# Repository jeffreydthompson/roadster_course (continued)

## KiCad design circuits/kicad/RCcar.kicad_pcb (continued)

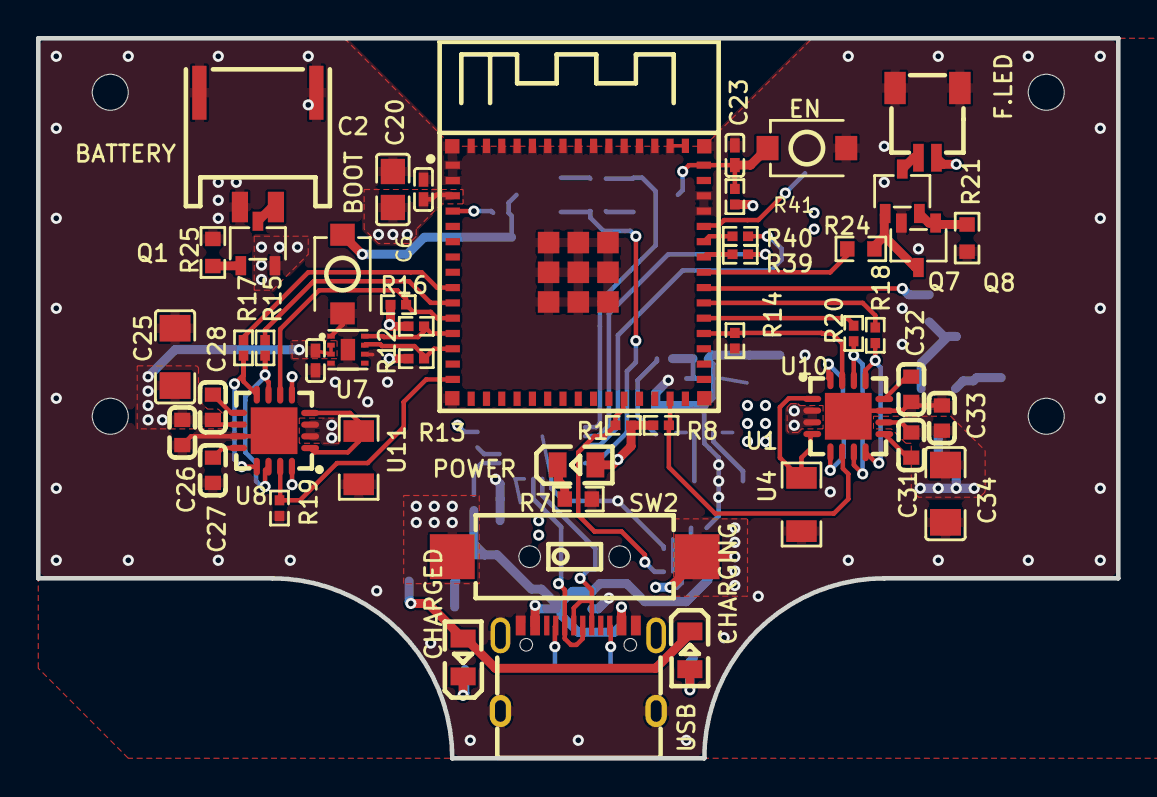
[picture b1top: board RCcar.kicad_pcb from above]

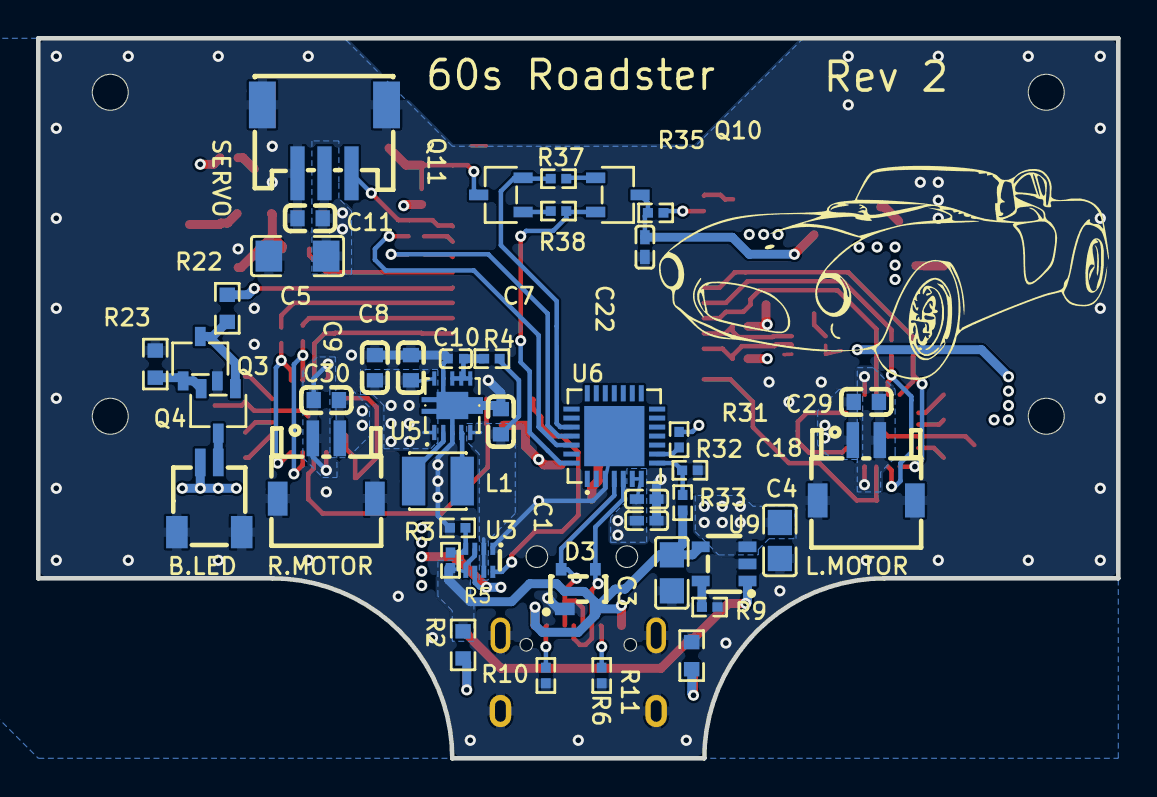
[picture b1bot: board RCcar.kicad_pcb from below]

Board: 4 copper layers, 60.0 x 40.0 mm, 95 parts (43 on the bottom side), 68 nets.

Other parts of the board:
Hole_gge8842846562267455: Hole_gge8842846562267455
Hole_gge8842846562267458: Hole_gge8842846562267458
Hole_gge8842846562267461: Hole_gge8842846562267461
Hole_gge8842846562267464: Hole_gge8842846562267464

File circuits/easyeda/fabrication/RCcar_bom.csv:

ID,Name,Designator,Footprint,Quantity,Manufacturer Part,Manufacturer,Supplier,Supplier Part,Price
"1","SM02B-SRSS-TB (LF)(SN)","B.LED,F.LED","CONN-SMD_2P-P1.00_SM02B-SRSS-TB-LF-SN","2","SM02B-SRSS-TB(LF)(SN)","JST","LCSC","C160402","0.133"
"2","PH2.0-2PWB","BATTERY","CONN-SMD_2P-P2.00_PH2.0-SPWB","1","PH-2P卧贴","BOOMELE(博穆精密)","LCSC","C47647","0.062"
"3","TS-1088-AR02016","BOOT,EN","SW-SMD_L3.9-W3.0-P4.45","2","TS-1088-AR02016","XUNPU(讯普)","LCSC","C720477","0.053"
"4","4.7uF","C1","C0402","1","CL05A475MP5NRNC","SAMSUNG(三星)","LCSC","C23733","0.017"
"5","22uF","C2","C0805","1","CL21A226MAQNNNE","SAMSUNG(三星)","LCSC","C45783","0.222"
"6","4.7uF","C3,C4","C0805","2","CL21A475KAQNNNE","SAMSUNG(三星)","LCSC","C1779","0.035"
"7","22uF","C5,C25,C34","C1206","3","HGC1206R7226K160NSPJ","Chinocera(华瓷)","LCSC","C7472972","0.156"
"8","100nF","C6,C18,C20,C22,C23","C0402_NEW","5","CL05B104KO5NNNC","SAMSUNG","LCSC","C1525","0.005"
"9","10uF","C7,C8,C9","C0603","3","CL10B106MQ8NRNC","SAMSUNG(三星)","LCSC","C3039698","0.091"
"10","100nF","C10","C0402","1","CL05B104KO5NNNC","SAMSUNG(三星)","LCSC","C1525","0.005"
"11","100nF","C11,C27,C32","C0603","3","CL10B104KO8NNNC","SAMSUNG(三星)","LCSC","C66501","0.009"
"12","2.2uF","C26,C33","C0603","2","CL10B225KP8NNNC","SAMSUNG(三星)","LCSC","C100082","0.028"
"13","10nF","C28,C31","C0603","2","CC0603KRX7R7BB103","YAGEO(国巨)","LCSC","C519406","0.006"
"14","100nF","C29,C30","C0603","2","CC0603KRX7R9BB104","YAGEO(国巨)","LCSC","C14663","0.014"
"15","0805G (Green)","CHARGED","LED0805-R-RD","1","KT-0805G","KENTO","LCSC","C2297","0.017"
"16","17-21SUYC/TR8","CHARGING","LED0805-R-RD","1","KT-0805黄灯","KENTO","LCSC","C2296","0.012"
"17","SP0503BAHTG","D3","SOT-143_L2.9-W1.3-P1.92-LS2.3-BR","1","SP0503BAHTG","Littelfuse","LCSC","C7074","0.264"
"18","2.2uH","L1","IND-SMD_L3.0-W3.0_FNR30XXS","1","SPH3015H2R2MT","Sunlord(顺络)","LCSC","C370424",""
"19","S2B-ZR-SM4A-TF(LF)(SN)","L.MOTOR,R.MOTOR","CONN-SMD_S2B-ZR-SM4A","2","S2B-ZR-SM4A-TF(LF)(SN)","JST","LCSC","C265329","0.222"
"20","FC-2012HRK-620D","POWER","LED0805-R-RD","1","NCD0805R1","国星光电","LCSC","C84256","0.014"
"21","SI2305CDS","Q1","SOT-23-3_L2.9-W1.6-P1.90-LS2.8-BR","1","SI2305CDS","TECH PUBLIC(台舟)","LCSC","C5182095","0.102"
"22","2SC2712-GR,LF(T","Q3,Q4,Q7,Q8","SOT-23-3_L2.9-W1.6-P1.90-LS2.8-BR","4","2SC2712-GR,LF(T","TOSHIBA","LCSC","C83447","0.031"
"23","SS8050-G","Q10,Q11","SOT-23-3_L2.9-W1.6-P1.90-LS2.8-BR","2","SS8050-G","CJ(江苏长电/长晶)","LCSC","C164886","0.017"
"24","5.1kΩ","R1,R5,R6,R9","R0402","4","0402WGF5101TCE","UNI-ROYAL(厚声)","LCSC","C25905","0.002"
"25","10kΩ","R2,R3,R8,R14,R16,R19,R37,R38,R41","R0402","9","0402WGF1002TCE","UniOhm","LCSC","C25744","0.003"
"26","100Ω","R4","R0402","1","0402WGF1000TCE","UNI-ROYAL(厚声)","LCSC","C25076","0.001"
"27","470Ω","R7,R10,R11","R0603","3","0603WAF4700T5E","UNI-ROYAL(厚声)","LCSC","C23179","0.002"
"28","4.7kΩ","R12,R13","R0402","2","0402WGF4701TCE","UNI-ROYAL(厚声)","LCSC","C25900","0.003"
"29","100Ω","R15,R17,R18,R20","R0402","4","RC0402FR-07100RL","YAGEO(国巨)","LCSC","C106232","0.002"
"30","22Ω","R21,R23","R0603","2","0603WAF220JT5E","UNI-ROYAL(厚声)","LCSC","C23345","0.002"
"31","1kΩ","R22,R24","R0603","2","MCT06030C1001FP500","Vishay Intertech","LCSC","C161809","0.042"
"32","100kΩ","R25","R0603","1","0603WAF1003T5E","UNI-ROYAL(厚声)","LCSC","C25803","0.003"
"33","1kΩ","R31","R0402","1","0402WGF1001TCE","UniOhm","LCSC","C11702","0.003"
"34","47.5kΩ","R32","R0402","1","0402WGF4752TCE","UniOhm","LCSC","C25896","0.002"
"35","22.1kΩ","R33","R0402","1","0402WGF2212TCE","UniOhm","LCSC","C43473","0.002"
"36","22Ω","R35","R0402","1","0402WGF220JTCE","UniOhm","LCSC","C25092","0.003"
"37","0Ω","R39,R40","R0402","2","0402WGF0000TCE","UniOhm","LCSC","C17168","0.003"
"38","HCZZ0323-3","SERVO","CONN-SMD_3P-P1.50_HCZZ0323-3","1","HCZZ0323-3","HC(虹成电子)","LCSC","C7433559","0.02"
"39","MS-12D08G3.5","SW2","SW-TH_MS-12D08G3.5","1","MS-12D08G3.5","HOOYA(皓宇电子)","LCSC","C2939255","0.154"
"40","ESP32-S3-MINI-1-N8","U1","BULETM-SMD_ESP32-S3-MINI-1-N8","1","ESP32-S3-MINI-1-N8","ESPRESSIF(乐鑫)","LCSC","C2913206","4.756"
"41","TPS2116DRLR","U3","SOT-583-8_L2.1-W1.6-P0.50-LS1.6-BL","1","TPS2116DRLR","TI(德州仪器)","LCSC","C3235557","0.403"
"42","50mΩ","U4,U11","R1206","2","FRM121WFR050TM","FOJAN(富捷)","LCSC","C7467249","0.035"
"43","TPS63001DRCR","U5","VSON-10_L3.0-W3.0-P0.50-TL-EP_TPS62410DRCR","1","TPS63001DRCR","TI(德州仪器)","LCSC","C28060","1.618"
"44","CP2102N-A02-GQFN28R","U6","QFN-28_L5.0-W5.0-P0.50-TL-EP3.3","1","CP2102N-A02-GQFN28R","SILICON LABS(芯科)","LCSC","C964632","1.837"
"45","MAX17048G+T10","U7","TDFN-8_L2.0-W2.0-P0.50-BL-EP1.2","1","MAX17048G+T10","ADI(亚德诺)/MAXIM(美信)","LCSC","C2682616","2.165"
"46","DRV8833RTYR","U8,U10","QFN-16_L4.0-W4.0-P0.65-TL-EP2.6","2","DRV8833RTYR","TI(德州仪器)","LCSC","C154936","2.411"
"47","MCP73831T-2ACI/OT","U9","SOT-23-5_L3.0-W1.7-P0.95-LS2.8-BR","1","MCP73831T-2ACI/OT","Microchip Tech","LCSC","C424093","0.791"
"48","TYPE-C 16PIN 2MD(073)","USB","USB-C-SMD_TYPE-C-6PIN-2MD-073","1","TYPE-C 16PIN 2MD(073)","SHOU HAN(首韩)","LCSC","C2765186","0.075"

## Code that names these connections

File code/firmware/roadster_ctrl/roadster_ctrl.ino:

#include "SteeringModule.h"
#include "DriveModule.h"
#include "BatteryModule.h"
#include "LightsModule.h"
#include "SerialCommander.h"
#include "BleCommander.h"
#include <driver/gpio.h>
#include <esp_sleep.h>

// Hardware Configuration
const int PIN_SERVO = 45;

// Left Motor (DRV8833)
const int PIN_MOTOR_LEFT_A = 6;
const int PIN_MOTOR_LEFT_B = 5;

// Right Motor (DRV8833)
const int PIN_MOTOR_RIGHT_A = 39;
const int PIN_MOTOR_RIGHT_B = 40;

// DRV8833 Control
const int PIN_L_SLEEP = 11;
const int PIN_R_SLEEP = 38;
const int PIN_L_FAULT = 7;
const int PIN_R_FAULT = 34;

// Battery I2C
const int PIN_I2C_SDA = 8;
const int PIN_I2C_SCL = 9;

// Power status: TPS2116 ST output (HIGH = USB power, LOW = battery)
const int PIN_POWER_ST = 26;

// Lights (F.LED and B.LED connectors)
const int PIN_WLED = 42; // front / headlights
const int PIN_RLED = 41; // rear / tail + brake

const bool ENABLE_SERIAL = false;
const bool ENABLE_STEERING = true;
const bool ENABLE_DRIVE = true;

// While shut down for low battery, wake this often to check for USB power
// or a recharged cell
const uint64_t LOW_BATTERY_CHECK_US = 60ULL * 1000000ULL;

// Driven low and held there through deep sleep: motors coasting with the
// DRV8833s asleep, servo signal off, lights off
const int SLEEP_LOW_PINS[] = {
  PIN_MOTOR_LEFT_A, PIN_MOTOR_LEFT_B, PIN_MOTOR_RIGHT_A, PIN_MOTOR_RIGHT_B,
  PIN_L_SLEEP, PIN_R_SLEEP, PIN_SERVO, PIN_WLED, PIN_RLED,
};

// Global Objects
SteeringModule steering(PIN_SERVO);
DriveModule driveLeft(PIN_MOTOR_LEFT_A, PIN_MOTOR_LEFT_B, PIN_L_SLEEP, PIN_L_FAULT);
DriveModule driveRight(PIN_MOTOR_RIGHT_A, PIN_MOTOR_RIGHT_B, PIN_R_SLEEP, PIN_R_FAULT);
BatteryModule battery(PIN_I2C_SDA, PIN_I2C_SCL, PIN_POWER_ST);
LightsModule lights(PIN_WLED, PIN_RLED);

// Control Interfaces
SerialCommander serialCmd(steering, driveLeft, driveRight);
BleCommander bleCmd(steering, driveLeft, driveRight, battery, lights);

void setup() {
  if (esp_sleep_get_wakeup_cause() == ESP_SLEEP_WAKEUP_TIMER) {
    // Only the low-battery shutdown sets a timer wake
    checkBatteryAfterShutdown();
  }
  releaseSleepPins();

  // Initialize Modules
  // Steering must attach first: ESP32Servo claims LEDC channel 0 directly,
  // and analogWrite() would otherwise have handed that channel to the lights,
  // leaving the servo and headlights sharing one PWM signal.
  if (ENABLE_STEERING) {
    steering.begin();
  }

  lights.begin();

  if (ENABLE_DRIVE) {
    driveLeft.begin();
    driveRight.begin();
  }

  battery.begin();
  
  // Correct for wiring: Left motor is physically reversed relative to Right
  if (ENABLE_DRIVE) {
    driveLeft.setInverted(true);
    driveRight.setInverted(true);
  }
  
  // Initialize Serial Commander
  if (ENABLE_SERIAL) {
    serialCmd.begin(115200);
  }

  // Initialize BLE Commander
  bleCmd.begin("Open Roadster");
}

void loop() {
  if (ENABLE_SERIAL) {
    serialCmd.update();
  }
  bleCmd.update();

  battery.update();
  BatteryState batteryState = battery.getState();
  lights.setLowBattery(batteryState == BatteryState::Low);
  lights.update();

  if (batteryState == BatteryState::Critical) {
    shutDownForLowBattery();
  }
}

// Stop, warn, and sleep before the cell is run flat. The car stays asleep
// until it's on USB power or the cell has been recharged, or the power
// switch is cycled.
void shutDownForLowBattery() {
  Serial.println("Battery critical: shutting down");
  driveLeft.setSpeed(0);
  driveRight.setSpeed(0);
  lights.flashWarning();
  sleepUntilBatteryCheck();
}

void sleepUntilBatteryCheck() {
  // GPIOs float in deep sleep unless held
  for (int pin : SLEEP_LOW_PINS) {
    pinMode(pin, OUTPUT);
    digitalWrite(pin, LOW);
    gpio_hold_en((gpio_num_t)pin);
  }
  gpio_deep_sleep_hold_en();

  esp_sleep_enable_timer_wakeup(LOW_BATTERY_CHECK_US);
  esp_deep_sleep_start();
}

void releaseSleepPins() {
  for (int pin : SLEEP_LOW_PINS) {
    gpio_hold_dis((gpio_num_t)pin);
  }
  gpio_deep_sleep_hold_dis();
}

// Woken from the low-battery shutdown: go straight back to sleep unless the
// car is on USB power or the cell has recovered
void checkBatteryAfterShutdown() {
  battery.begin();
  delay(500); // let the fuel gauge take a reading after its reset

  bool onUsb = battery.isOnUsbPower();
  float volts = battery.readVoltageNow();
  if (!onUsb && volts < BatteryModule::RECOVER_VOLTAGE) {
    sleepUntilBatteryCheck();
  }
}

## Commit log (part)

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2026-01-23 commit printed parts
2026-02-06 3d model insert size edit. stub out firmware servo module
2026-02-07 firmware development
2026-02-07 fix motor inversion
